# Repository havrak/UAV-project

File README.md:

# UAV project

This repository contains all resource that comprised my final thesis for my senior year in high school.
Main purpose was to create UAV platform based on Raspberry Pi.

Codebase is this project is rather bad by my current standards and is heavily impacted by the fact it was essentially my first hardware related project.
Not to mention my experience with C++ was rather limited at the time.

Desktop client is written in C++ using Gtk3 and is used to control the drone and display telemetry data.
UI wise it's really bad, and code itself doesn't land much in a way for easy rewrite.

Drone side might fare a bit better, but it's still not great.
Usage of threads is rather questionable and OOP design patterns were a hip new thing for me at the time and not something I was able to use properly.

Thus some parts of codebase are overengineered and some lack any flexibility and don't deserve much other than deletion.

In my 3rd semester of university I've made addition to this project in a shape of proper custom PCB to house drone electronics.

I might rewrite this project in the future, but time is a limited resource and school+work take priority.
Though if rewrite happens, it will be wholly different project.
* camera streaming with gstreamer has never worked as well as I wanted it to
* using Wi-Fi for communication was never ideal (drone was acting as AP)
* codebase and communication protocol needs to be much more open to allow different configurations of hardware
* desktop client needs to be rewritten from scratch and preferably in Qt
* way more robust compilation and deployment process is needed (Kconfig, hierarchical Makefiles, etc.)

# Libraries and toolkits
* [WT901B library](https://github.com/havrak/Raspberry-JY901-Serial-I2C)
* [INA226 library](https://github.com/havrak/raspberry-pi-ina226)
* [PCA9685 library](https://github.com/havrak/PCA9685-rpi)
* [inih (INI Not Invented Here)](https://github.com/benhoyt/inih)
* Gtk3
* crp, fmt
* WiringPi

# Photos

### UAV Photos

### Board

# Credits
* textures for desktop client originate from [marek-cel/QFlightinstruments](https://github.com/marek-cel/QFlightinstruments)

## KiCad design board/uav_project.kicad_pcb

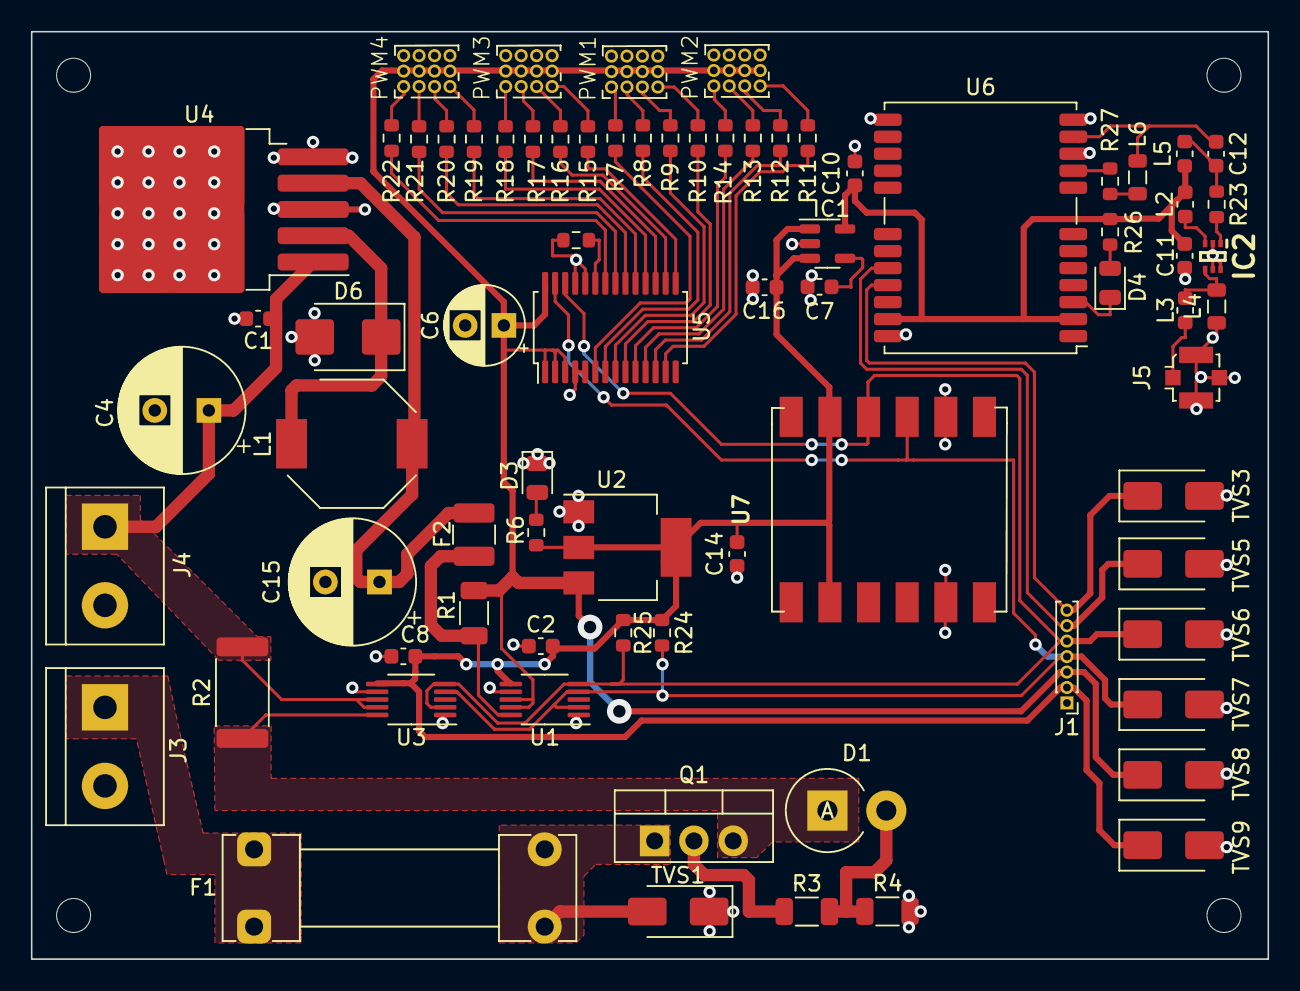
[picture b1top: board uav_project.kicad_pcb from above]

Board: 2 copper layers, 80.0 x 60.0 mm, 80 parts (0 on the bottom side), 61 nets.

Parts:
C1, C2, C7, C8, C11, C14: 100n; C_0603_1608Metric
C4, C15: 100u; CP_Radial_D8.0mm_P3.50mm
C6: 33u; CP_Radial_D5.0mm_P2.50mm
C10, C16: 1p; C_0603_1608Metric
C12: 100p; C_0603_1608Metric
D1: 1N53xxB; D_DO-201_P3.81mm_Vertical_AnodeUp
D3, D4: LED; LED_0805_2012Metric
D6: SS210; D_SMB
F1: Fuse; Fuseholder_Clip-5x20mm_Littelfuse_111_Lateral_P18.80x5.00mm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
F2: Polyfuse; Fuse_1210_3225Metric
H1, H2, H3, H4: MountingHole; MountingHole_2.2mm_M2
IC1: RT9193-33GB; SOT-23-5
IC2: NJG1130KA1-TE1; SOTFL50P160X60-6N
J1: Conn_01x07; PinHeader_1x07_P1.00mm_Vertical
J3: Bat IN Terminal; TerminalBlock_bornier-2_P5.08mm
J4: Bat OUT Terminal; TerminalBlock_bornier-2_P5.08mm
J5: Conn_Coaxial; U.FL_Molex_MCRF_73412-0110_Vertical
L1: 47u; L_Bourns-SRU8043
L2, L3: 8.7n; L_0603_1608Metric
L4, L6: 18n; L_0805_2012Metric
L5: 47n; L_0603_1608Metric
PWM1, PWM2, PWM3, PWM4: conn_03x04_Pin; PinHeader_3x04
Q1: PMOS; TO-220-3_Vertical
R1: 20m; R_1206_3216Metric
R2: 20m; R_2512_6332Metric
R3: 100; R_1206_3216Metric
R4: 10k; R_1206_3216Metric
R5: 10k; R_0603_1608Metric
R6, R26: 470; R_0603_1608Metric
R7, R8, R9, R10, R11, R12, R13, R14, R15, R16, R17, R18, R19, R20, R21, R22: 220; R_0603_1608Metric
R23, R27: 10; R_0603_1608Metric
R24, R25: 4.7k; R_0603_1608Metric
TVS1, TVS3, TVS5, TVS6, TVS7, TVS8, TVS9: SMAJ30CA; D_SMA
U1, U3: INA226; VSSOP-10_3x3mm_P0.5mm
U2: AMS1117-3.3; SOT-223-3_TabPin2
U4: LM2596S-5; TO-263-5_TabPin3
U5: PCA9685PW; TSSOP-28_4.4x9.7mm_P0.65mm
U6: NEO-M7N; ublox_NEO
U7: WT901B

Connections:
+3V3: C2.1, C8.1, C14.1, C16.2, IC1.1 (VIN), IC1.3 (EN), J1.2, R6.1, R24.1, R25.1, TVS9.1 (A1), U1.6 (VS), U2.2 (VO), U3.6 (VS), U7.2 (VCC)
+5V: C6.1, J1.3, PWM1.2, PWM1.5, PWM1.8, PWM1.11, PWM2.2, PWM2.5, PWM2.8, PWM2.11, PWM3.2, PWM3.5, PWM3.8, PWM3.11, PWM4.2, PWM4.5, PWM4.8, PWM4.11, R1.2, TVS8.1 (A1), U1.8 (Vbus), U1.9 (Vin-), U2.3 (VI), U5.1 (A0), U5.2 (A1), U5.3 (A2), U5.28 (VDD)
/GPS module/+3V3 LN: C10.2, C11.1, IC1.5 (VOUT), L2.1, L5.1, R26.2, U6.2 (D_SEL), U6.23 (VCC)
/GPS module/RF_IN: C12.1, L6.2, U6.11 (RF_IN)
/GPS module/VCC_RF: R27.2, U6.9 (VCC_RF)
/Power managment/5V SENSE IN: F2.2, R1.1, U1.10 (Vin+)
/Power managment/BAT SENSE IN: D1.1 (K), Q1.3 (S), R2.1, U3.10 (Vin+)
/Power managment/BAT SENSE OUT: C1.1, C4.1, J4.1, R2.2, U3.8 (Vbus), U3.9 (Vin-), U4.1 (VIN)
/Power managment/BAT UNSAFE: F1.1, F1.2, J3.1, Q1.1 (D), TVS1.2 (A2)
/Servo driver/PWM0: R7.2, U5.6 (LED0)
/Servo driver/PWM1: R8.2, U5.7 (LED1)
/Servo driver/PWM2: R9.2, U5.8 (LED2)
/Servo driver/PWM3: R10.2, U5.9 (LED3)
/Servo driver/PWM4: R14.2, U5.10 (LED4)
/Servo driver/PWM5: R13.2, U5.11 (LED5)
/Servo driver/PWM6: R12.2, U5.12 (LED6)
/Servo driver/PWM7: R11.2, U5.13 (LED7)
/Servo driver/PWM8: R15.2, U5.15 (LED8)
/Servo driver/PWM9: R16.2, U5.16 (LED9)
/Servo driver/PWM10: R17.2, U5.17 (LED10)
/Servo driver/PWM11: R18.2, U5.18 (LED11)
/Servo driver/PWM12: R19.2, U5.19 (LED12)
/Servo driver/PWM13: R20.2, U5.20 (LED13)
/Servo driver/PWM14: R21.2, U5.21 (LED14)
/Servo driver/PWM15: R22.2, U5.22 (LED15)
GND: C1.2, C2.2, C4.2, C6.2, C7.1, C8.2, C10.1, C11.2, C14.2, C15.2, C16.1, D3.1 (K), D6.2 (A), IC1.2 (GND), IC2.2 (GND_1), IC2.5 (GND_2), IC2.6 (GND_3), J1.1, J3.2, J4.2, J5.2 (Ext), L4.1, PWM1.3, PWM1.6, PWM1.9, PWM1.12, PWM2.3, PWM2.6, PWM2.9, PWM2.12, PWM3.3, PWM3.6, PWM3.9, PWM3.12, PWM4.3, PWM4.6, PWM4.9, PWM4.12, R4.2, R5.1, TVS1.1 (A1), TVS3.2 (A2), TVS5.2 (A2), TVS6.2 (A2), TVS7.2 (A2), TVS8.2 (A2), TVS9.2 (A2), U1.1 (A1), U1.7 (GND), U2.1 (GND), U3.1 (A1), U3.7 (GND), U4.3 (GND), U4.5 (~ON/OFF), U5.4 (A3), U5.5 (A4), U5.24 (A5), U5.25 (EXTCLK), U6.10 (GND), U6.12 (GND), U6.13 (GND), U6.24 (GND), U7.5 (GND)
unnamed: C12.2, L5.2, R23.1
unnamed: D1.2 (A), R3.2, R4.1
unnamed: D3.2 (A), R6.2
unnamed: D4.2 (A), R26.1
unnamed: D4.1 (K), U6.3 (TIMEPULSE)
unnamed: D6.1 (K), L1.1, U4.2 (OUT)
unnamed: C7.2, IC1.4 (BP)
unnamed: IC2.4 (RF_IN), L3.1, L4.2
unnamed: IC2.1 (RF_OUT), R23.2
unnamed: IC2.3 (VDD), L2.2
unnamed: J5.1 (In), L3.2
unnamed: L6.1, R27.1
unnamed: PWM1.1, R7.1
unnamed: PWM1.4, R8.1
unnamed: PWM1.7, R9.1
unnamed: PWM1.10, R10.1
unnamed: PWM2.1, R14.1
unnamed: PWM2.4, R13.1
unnamed: PWM2.7, R12.1
unnamed: PWM2.10, R11.1
unnamed: PWM3.1, R18.1
unnamed: PWM3.4, R17.1
unnamed: PWM3.7, R16.1
unnamed: PWM3.10, R15.1
unnamed: PWM4.1, R22.1
unnamed: PWM4.4, R21.1
unnamed: PWM4.7, R20.1
unnamed: PWM4.10, R19.1
unnamed: Q1.2 (G), R3.1
unnamed: C15.1, F2.1, L1.2, U4.4 (FB)
unnamed: R5.2, U5.23 (~OE)
RX: J1.7, TVS3.1 (A1), U6.21 (RXD/SPI_MOSI)
SDA: J1.4, R24.2, TVS7.1 (A1), U1.2 (A0), U1.4 (SDA), U3.4 (SDA), U5.27 (SDA), U7.9 (SDA)
SLC: J1.5, R25.2, TVS6.1 (A1), U1.5 (SCL), U3.2 (A0), U3.5 (SCL), U5.26 (SCL), U7.8 (SLC)
TX: J1.6, TVS5.1 (A1), U6.20 (TXD/SPI_MISO)

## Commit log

2021-09-06 addded LICENSE
2021-10-28 fucnking kill me
2021-10-29 small changes, nothing for drone works yet
2021-10-31 fixed singleton, updateLoop and CMake file
2021-11-21 nothing new
2021-11-21 forgot to commit servoControl.h
2021-12-01 started writing controller interface
2021-12-03 More work on controller
2021-12-05 Trying to get servo to work
2021-12-05 Kill me
2021-12-08 Integration of ina226 library
2022-01-13 Gave up on stupid WT901B FUCK
2022-01-14 Moved WT901 to I2C, intergrated GPS
2022-01-16 Not sure what changed
2022-01-16 Controller works, renamed classes
2022-01-17 Minor cleanup
2022-01-18 Mid work commit - communication+controller
2022-01-18 Work on communication interface
2022-02-02 More work on communication
2022-02-04 Small work on communication
2022-02-06 Created something
2022-02-07 Just commiting before overhaul
2022-02-07 Reworkied fixing of messages via circular buffer
2022-02-07 Now compiles, not tested
2022-02-08 Added threadpool to send data
2022-02-08 Added file with rough protocol specification
2022-02-09 Minor work
2022-02-11 Small work
2022-02-13 more work
2022-02-13 Some more work on pi side
2022-02-13 Some more work
2022-02-13 Desktop client now compiles and doen't crash imediately
2022-02-14 pain
2022-02-15 Rewrote sending and processing structures to objects
2022-02-15 Rewrote sending and processing structures to objects on desktop side
2022-02-15 Fixed the stupid error
2022-02-17 not much new
2022-02-20 More debugging yay
2022-02-20 Works
2022-02-21 Added configuration files for rpi0
2022-02-22 Communication seems to work
2022-02-23 Revorked error sending system
2022-02-23 minor changes
2022-02-24 Fixed interaction with text buffer, rescale video
2022-02-24 bugfixes
2022-02-25 bugfix
2022-02-26 Controll works, ready to fly
2022-02-26 Started work on PID
2022-02-27 added PID controller
2022-02-27 debugging
2022-02-27 Zpracována první část dokumentace
2022-02-28 added docs on client side
2022-02-28 added docs on raspberry pi side
2022-02-28 Documentation finished
2022-02-28 Minor clean up
2022-03-03 Added poster
2022-03-06 Moved to my wesion of PCA9685 library
2022-03-06 Added presentation
2022-03-18 Did rewrite for camera, started implementing configuration file logic
2022-03-20 Indicator now works
2022-03-27 Small changes
2022-03-28 Midwork
2022-03-29 Detection of sensors now works, configurable adresses of i2c devices
2022-03-30 Finishing touches before submitting project
2022-04-17 Found type in configuration which resulted in WT901B not working
2022-04-19 Better cleanup for closing for desktop application
2022-05-15 Minor fixes
2022-06-06 Started work on airmap.com integration
2022-06-07 Fetching data from airmap works
2022-06-17 Reworked internal layout of hardware
2022-06-19 integration to airmap.com is complete
2022-06-19 Updated photos, eddit stl file with mount of components
2022-06-19 Added map integration
2023-05-16 nuked current structure of drone side
2023-10-12 Started work on board
2023-10-14 Hopefully finished schema for pcb
2023-10-15 Minor changes in shchema for PCB
2023-10-15 Reverted sensor logic back from old commit
2023-10-18 Updated schme to comply with electrical rules checker, prepared sensor logic for rewrite
2023-10-22 More work in reformating drone side of codebase to be semi usable
2023-10-24 Started work on PCB design, more work on rewritting firmware to be semi usable
2023-10-25 More work on PCB design
2023-10-25 First version of PCB finished
2023-10-27 Minor improvements to board design
2023-10-28 Put some more space between 16V and 5V line
2023-10-30 Cleanup on drone side, to make code more bearable and simple
2023-10-31 Minor improvement to the board
2023-11-19 Compilation on bananpi works
2023-11-19 Added BOM, changed readme
2023-11-30 Changed example of drone configuration, badly added option to set shunt value
